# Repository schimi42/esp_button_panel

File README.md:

# esp_button_panel
PCB for push button panel, based on ESP8266

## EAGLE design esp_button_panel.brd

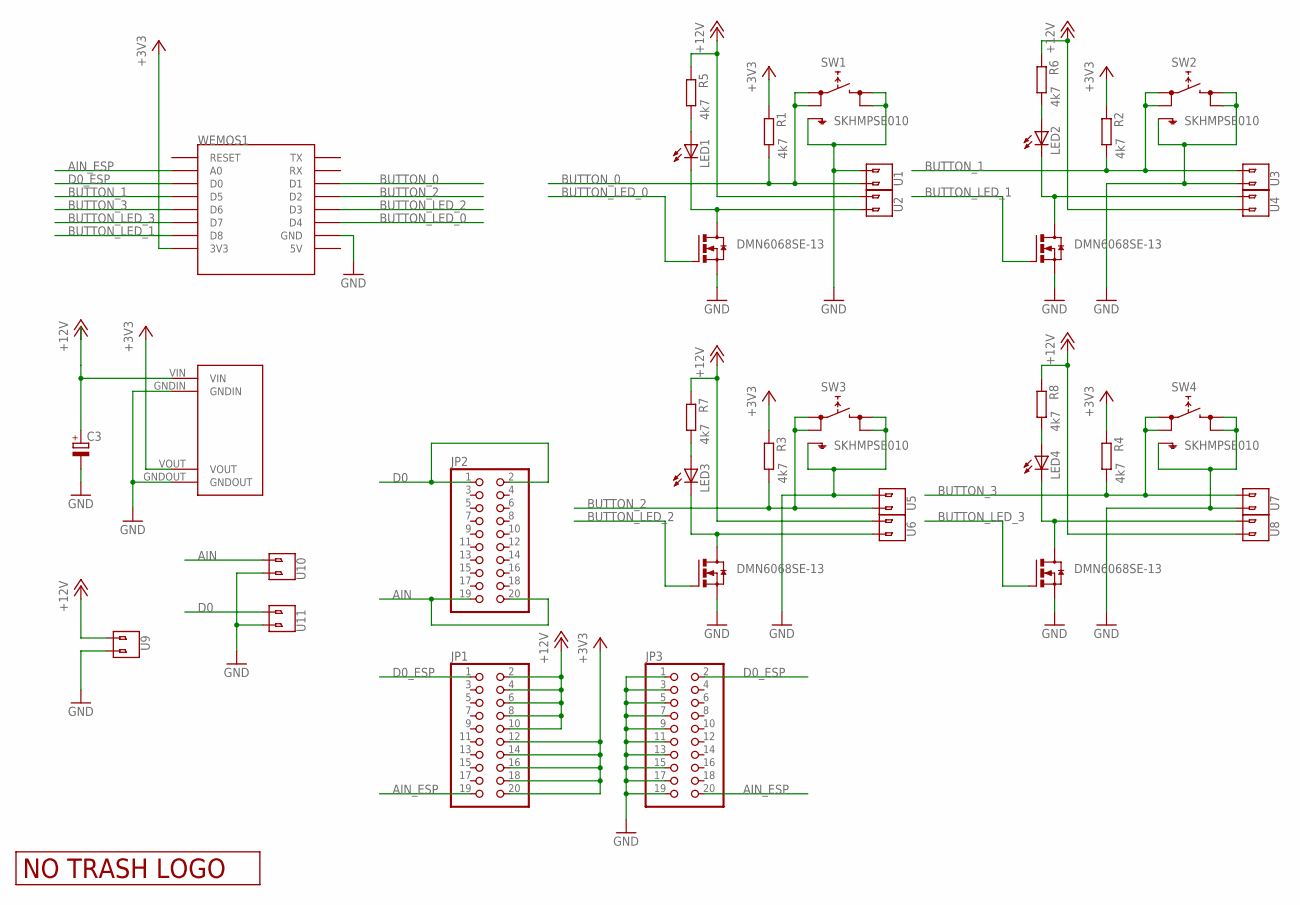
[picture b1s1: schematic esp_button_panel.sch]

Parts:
C3: CPOL-EU150CLZ-0810; 150CLZ-0810
JP1, JP2, JP3: PINHD-2X10; 2X10
LED1, LED2, LED3, LED4: LEDCHIPLED_0805; CHIPLED_0805
R1, R2, R3, R4, R5, R6, R7, R8: 4k7; M0805
SW1, SW2, SW3, SW4: SKHMPSE010; SKHMPXE010
T1, T2, T3, T4: DMN6068SE-13; SOT223
U1, U2, U3, U4, U5, U6, U7, U8, U9, U10, U11: V1; 2_SCREW_PIN
U$1: LOGO_NO_TRASHNO_TRASH; LOGO_ROHS_NO_TRASH
U$3: MP1584EN
WEMOS1: WEMOS-D1-MINI

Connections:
+3V3: JP1.12, JP1.14, JP1.16, JP1.18, JP1.20, R1.1, R2.1, R3.1, R4.1, U$3.VOUT, WEMOS1.3V3
+12V: C3.+, JP1.2, JP1.4, JP1.6, JP1.8, JP1.10, R5.1, R6.1, R7.1, R8.1, U2.P$1 (1), U4.P$2 (2), U6.P$1 (1), U8.P$2 (2), U9.P$2 (2), U$3.VIN
AIN: JP2.19, JP2.20, U10.P$2 (2)
AIN_ESP: JP1.19, JP3.20, WEMOS1.A0
BUTTON_0: R1.2, SW1.1 (1.1), SW1.2 (1.2), U1.P$2 (2), WEMOS1.D1
BUTTON_1: R2.2, SW2.1 (1.1), SW2.2 (1.2), U3.P$1 (1), WEMOS1.D5
BUTTON_2: R3.2, SW3.1 (1.1), SW3.2 (1.2), U5.P$2 (2), WEMOS1.D2
BUTTON_3: R4.2, SW4.1 (1.1), SW4.2 (1.2), U7.P$1 (1), WEMOS1.D6
BUTTON_LED_0: T1.1 (G), WEMOS1.D4
BUTTON_LED_1: T2.1 (G), WEMOS1.D8
BUTTON_LED_2: T3.1 (G), WEMOS1.D3
BUTTON_LED_3: T4.1 (G), WEMOS1.D7
D0: JP2.1, JP2.2, U11.P$2 (2)
D0_ESP: JP1.1, JP3.2, WEMOS1.D0
GND: C3.-, JP3.1, JP3.3, JP3.5, JP3.7, JP3.9, JP3.11, JP3.13, JP3.15, JP3.17, JP3.19, SW1.3 (2.1), SW1.4 (2.2), SW1.5 (SH), SW2.3 (2.1), SW2.4 (2.2), SW2.5 (SH), SW3.3 (2.1), SW3.4 (2.2), SW3.5 (SH), SW4.3 (2.1), SW4.4 (2.2), SW4.5 (SH), T1.3 (S), T2.3 (S), T3.3 (S), T4.3 (S), U1.P$1 (1), U3.P$2 (2), U5.P$1 (1), U7.P$2 (2), U9.P$1 (1), U10.P$1 (1), U11.P$1 (1), U$3.GNDIN, U$3.GNDOUT, WEMOS1.GND
unnamed: LED1.C, T1.2 (D), T1.4 (D), U2.P$2 (2)
unnamed: LED2.A, R6.2
unnamed: LED1.A, R5.2
unnamed: LED3.A, R7.2
unnamed: LED2.C, T2.2 (D), T2.4 (D), U4.P$1 (1)
unnamed: LED4.A, R8.2
unnamed: LED3.C, T3.2 (D), T3.4 (D), U6.P$2 (2)
unnamed: LED4.C, T4.2 (D), T4.4 (D), U8.P$1 (1)

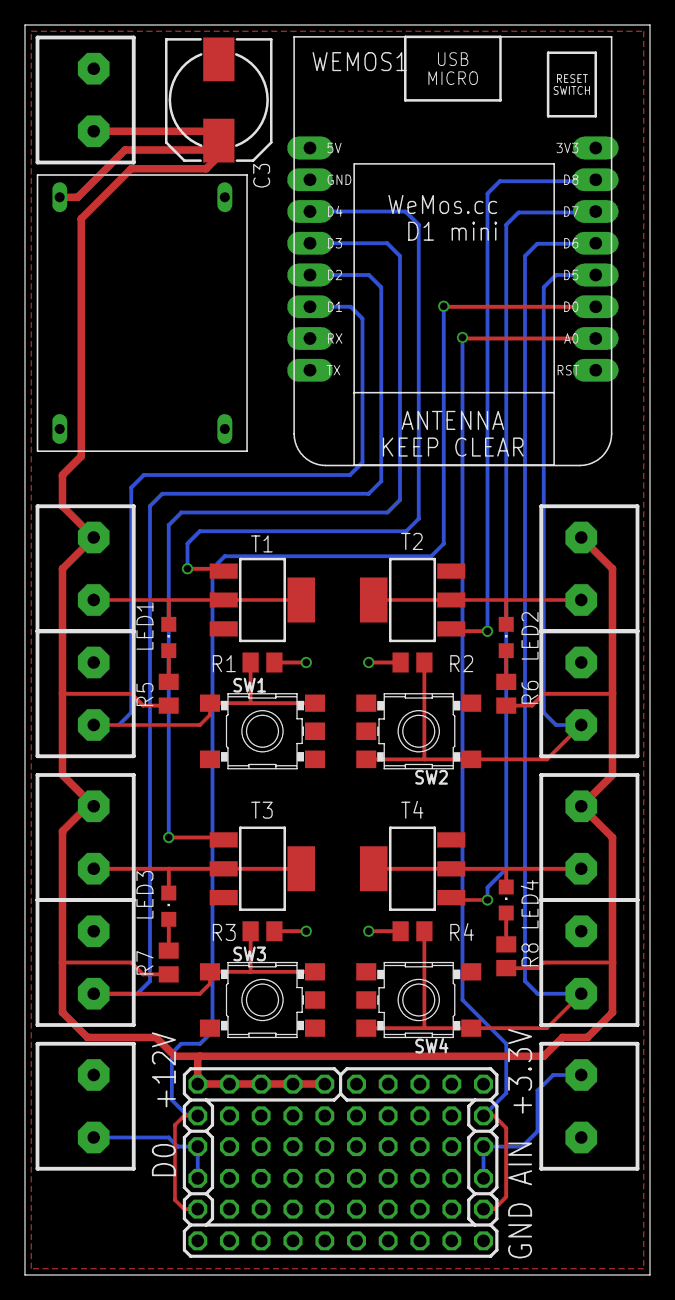
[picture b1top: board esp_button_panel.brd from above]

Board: 2 copper layers, 50.0 x 100.0 mm, 38 parts (1 on the bottom side), 23 nets.

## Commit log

2017-04-17 PCB order version

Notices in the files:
parts and their libraries:
JKW_CHIP: License : http://creativecommons.org/licenses/by-sa/3.0
(Creative Commons 3.0)
